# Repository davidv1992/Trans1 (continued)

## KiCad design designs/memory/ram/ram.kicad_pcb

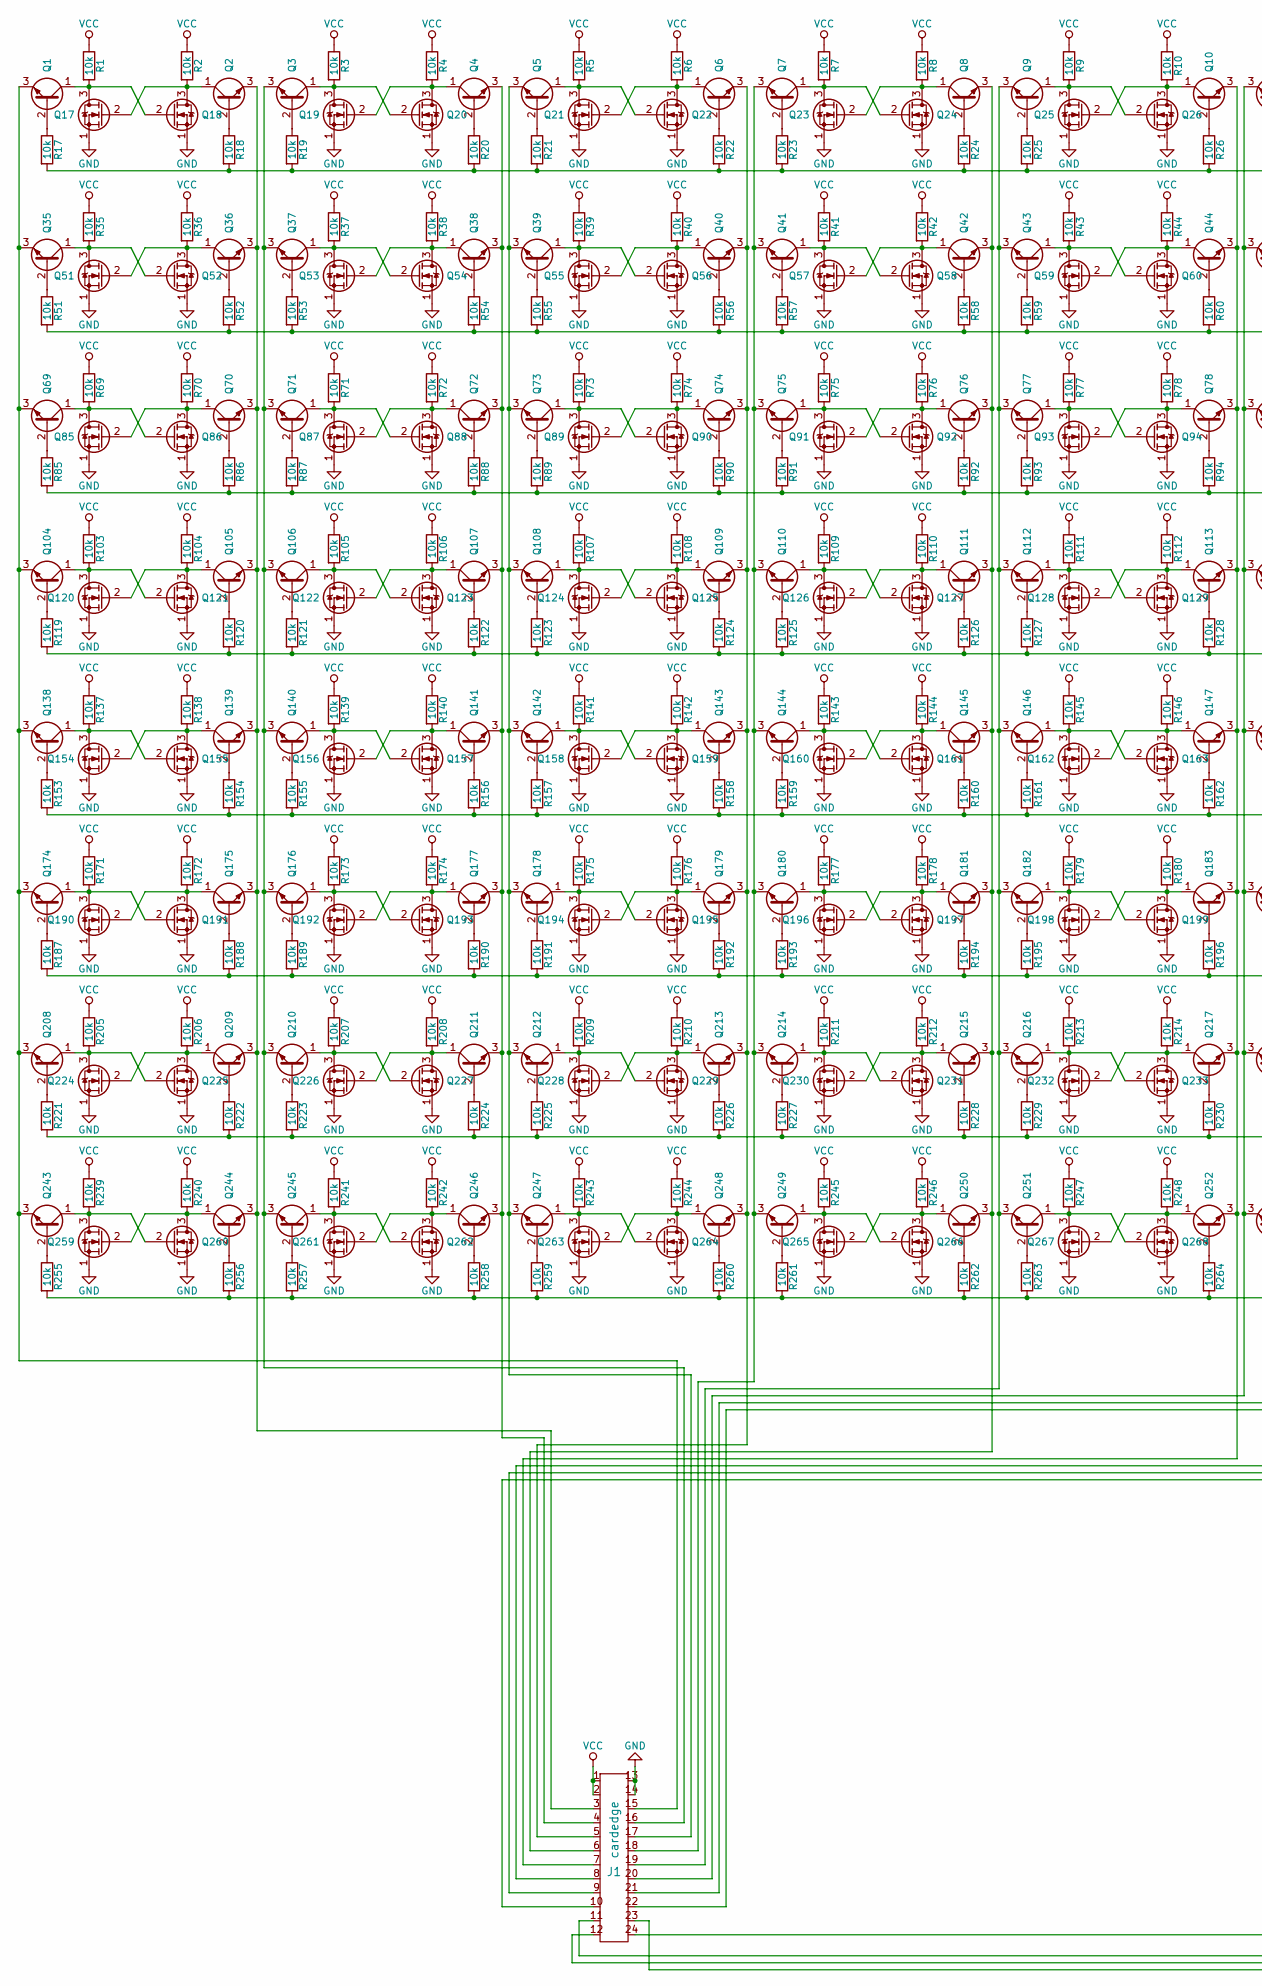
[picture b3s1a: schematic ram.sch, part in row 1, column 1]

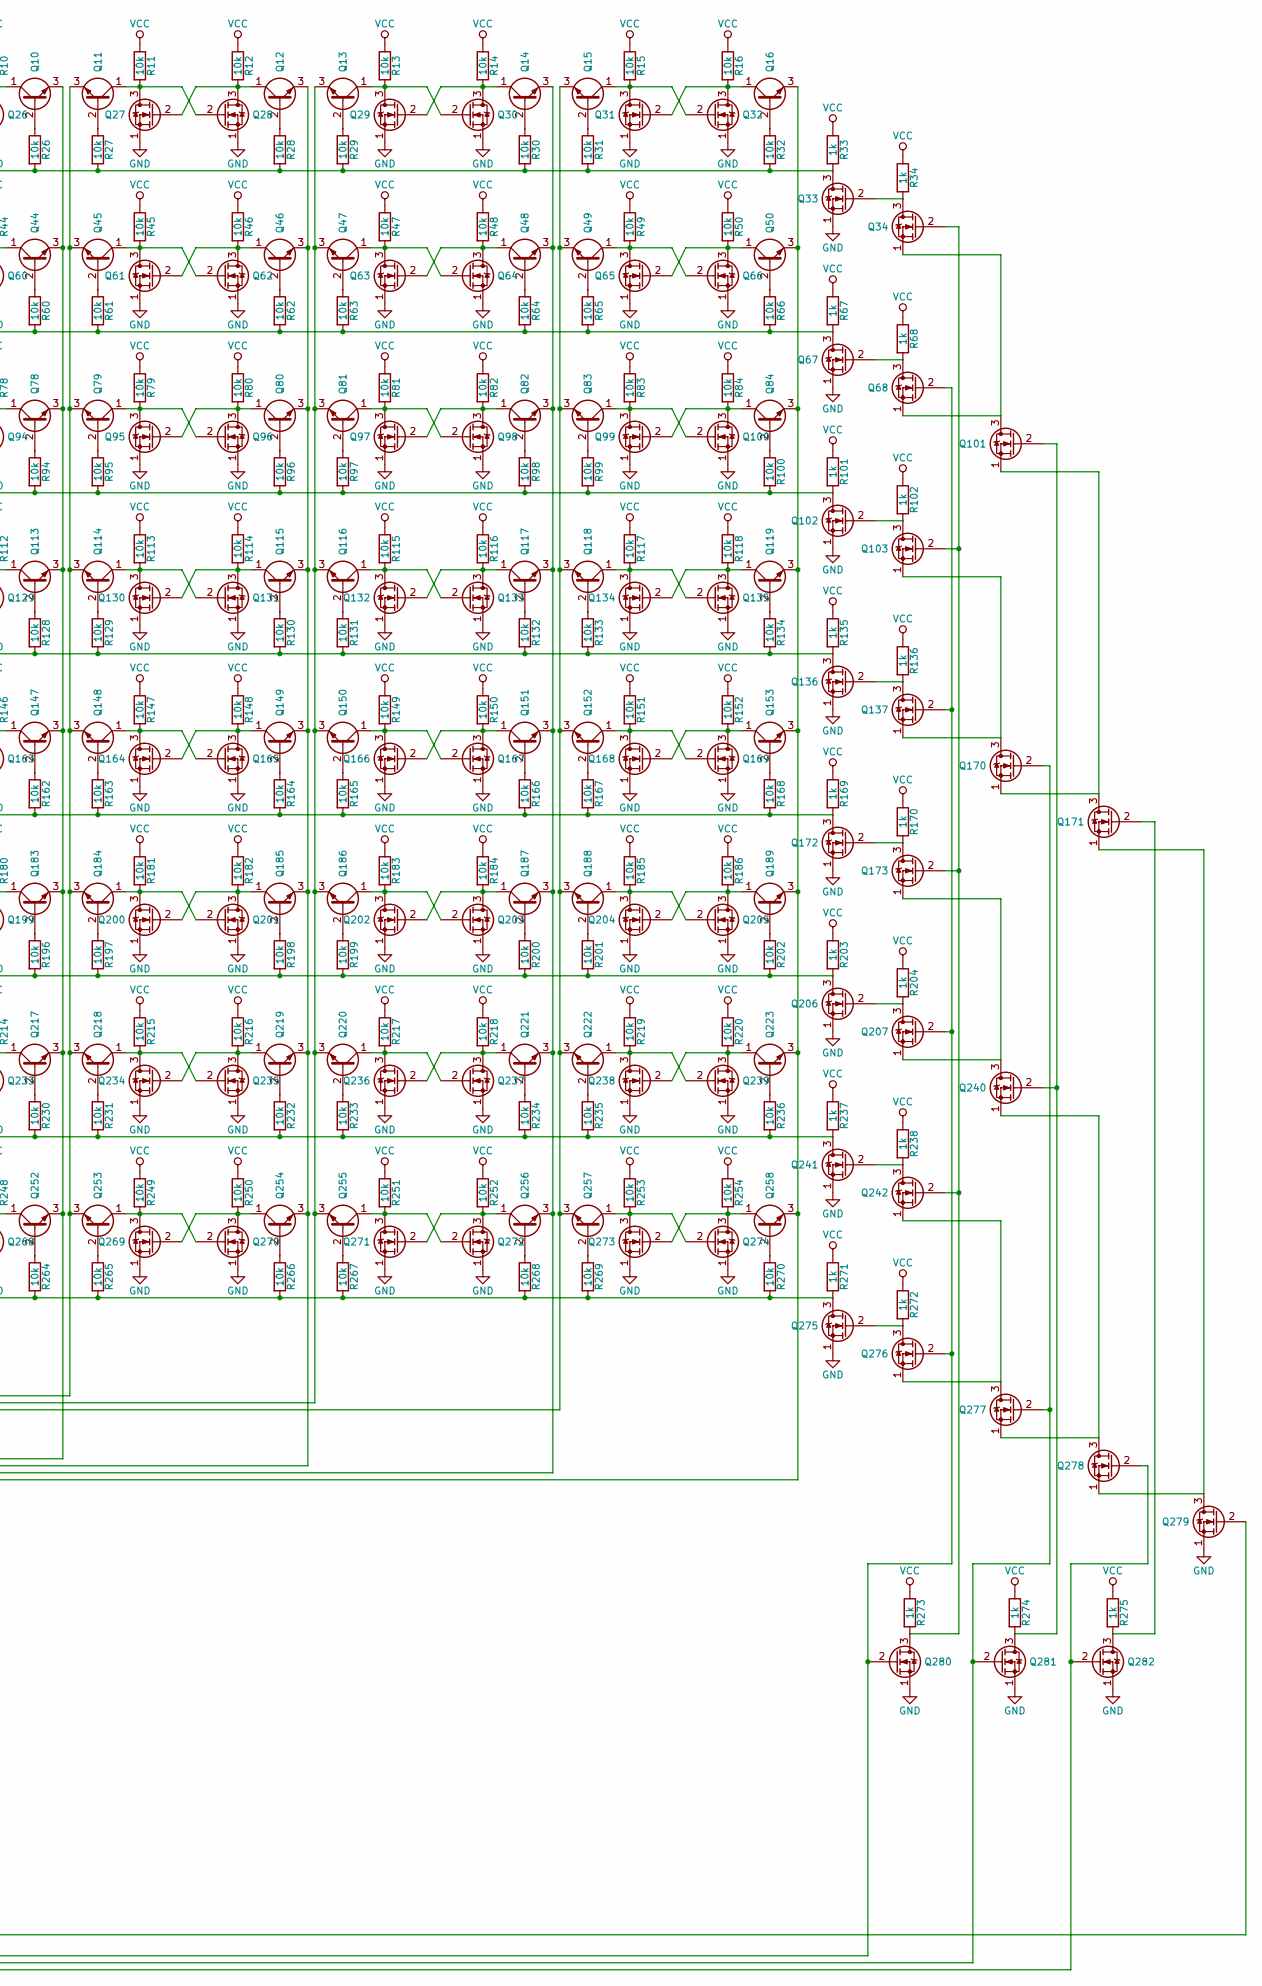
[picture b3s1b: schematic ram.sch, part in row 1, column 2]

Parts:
J1: cardedge; cardedge_12p
Q1, Q2, Q3, Q4, Q5, Q6, Q7, Q8, Q9, Q10, Q11, Q12, Q13, Q14, Q15, Q16, Q35, Q36, Q37, Q38, Q39, Q40, Q41, Q42, Q43, Q44, Q45, Q46, Q47, Q48, Q49, Q50, Q69, Q70, Q71, Q72, Q73, Q74, Q75, Q76, Q77, Q78, Q79, Q80, Q81, Q82, Q83, Q84, Q104, Q105, Q106, Q107, Q108, Q109, Q110, Q111, Q112, Q113, Q114, Q115, Q116, Q117, Q118, Q119, Q138, Q139, Q140, Q141, Q142, Q143, Q144, Q145, Q146, Q147, Q148, Q149, Q150, Q151, Q152, Q153, Q174, Q175, Q176, Q177, Q178, Q179, Q180, Q181, Q182, Q183, Q184, Q185, Q186, Q187, Q188, Q189, Q208, Q209, Q210, Q211, Q212, Q213, Q214, Q215, Q216, Q217, Q218, Q219, Q220, Q221, Q222, Q223, Q243, Q244, Q245, Q246, Q247, Q248, Q249, Q250, Q251, Q252, Q253, Q254, Q255, Q256, Q257, Q258: BC547; TO-92-BJT
Q17, Q18, Q19, Q20, Q21, Q22, Q23, Q24, Q25, Q26, Q27, Q28, Q29, Q30, Q31, Q32, Q33, Q34, Q51, Q52, Q53, Q54, Q55, Q56, Q57, Q58, Q59, Q60, Q61, Q62, Q63, Q64, Q65, Q66, Q67, Q68, Q85, Q86, Q87, Q88, Q89, Q90, Q91, Q92, Q93, Q94, Q95, Q96, Q97, Q98, Q99, Q100, Q101, Q102, Q103, Q120, Q121, Q122, Q123, Q124, Q125, Q126, Q127, Q128, Q129, Q130, Q131, Q132, Q133, Q134, Q135, Q136, Q137, Q154, Q155, Q156, Q157, Q158, Q159, Q160, Q161, Q162, Q163, Q164, Q165, Q166, Q167, Q168, Q169, Q170, Q171, Q172, Q173, Q190, Q191, Q192, Q193, Q194, Q195, Q196, Q197, Q198, Q199, Q200, Q201, Q202, Q203, Q204, Q205, Q206, Q207, Q224, Q225, Q226, Q227, Q228, Q229, Q230, Q231, Q232, Q233, Q234, Q235, Q236, Q237, Q238, Q239, Q240, Q241, Q242, Q259, Q260, Q261, Q262, Q263, Q264, Q265, Q266, Q267, Q268, Q269, Q270, Q271, Q272, Q273, Q274, Q275, Q276, Q277, Q278, Q279, Q280, Q281, Q282: 2N7000; TO-92-FET
R1, R2, R3, R4, R5, R6, R7, R8, R9, R10, R11, R12, R13, R14, R15, R16, R17, R18, R19, R20, R21, R22, R23, R24, R25, R26, R27, R28, R29, R30, R31, R32, R35, R36, R37, R38, R39, R40, R41, R42, R43, R44, R45, R46, R47, R48, R49, R50, R51, R52, R53, R54, R55, R56, R57, R58, R59, R60, R61, R62, R63, R64, R65, R66, R69, R70, R71, R72, R73, R74, R75, R76, R77, R78, R79, R80, R81, R82, R83, R84, R85, R86, R87, R88, R89, R90, R91, R92, R93, R94, R95, R96, R97, R98, R99, R100, R103, R104, R105, R106, R107, R108, R109, R110, R111, R112, R113, R114, R115, R116, R117, R118, R119, R120, R121, R122, R123, R124, R125, R126, R127, R128, R129, R130, R131, R132, R133, R134, R137, R138, R139, R140, R141, R142, R143, R144, R145, R146, R147, R148, R149, R150, R151, R152, R153, R154, R155, R156, R157, R158, R159, R160, R161, R162, R163, R164, R165, R166, R167, R168, R171, R172, R173, R174, R175, R176, R177, R178, R179, R180, R181, R182, R183, R184, R185, R186, R187, R188, R189, R190, R191, R192, R193, R194, R195, R196, R197, R198, R199, R200, R201, R202, R205, R206, R207, R208, R209, R210, R211, R212, R213, R214, R215, R216, R217, R218, R219, R220, R221, R222, R223, R224, R225, R226, R227, R228, R229, R230, R231, R232, R233, R234, R235, R236, R239, R240, R241, R242, R243, R244, R245, R246, R247, R248, R249, R250, R251, R252, R253, R254, R255, R256, R257, R258, R259, R260, R261, R262, R263, R264, R265, R266, R267, R268, R269, R270: 10k; R_small
R33, R34, R67, R68, R101, R102, R135, R136, R169, R170, R203, R204, R237, R238, R271, R272, R273, R274, R275: 1k; R_small

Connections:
GND: J1.13, J1.14, Q17.1 (S), Q18.1 (S), Q19.1 (S), Q20.1 (S), Q21.1 (S), Q22.1 (S), Q23.1 (S), Q24.1 (S), Q25.1 (S), Q26.1 (S), Q27.1 (S), Q28.1 (S), Q29.1 (S), Q30.1 (S), Q31.1 (S), Q32.1 (S), Q33.1 (S), Q51.1 (S), Q52.1 (S), Q53.1 (S), Q54.1 (S), Q55.1 (S), Q56.1 (S), Q57.1 (S), Q58.1 (S), Q59.1 (S), Q60.1 (S), Q61.1 (S), Q62.1 (S), Q63.1 (S), Q64.1 (S), Q65.1 (S), Q66.1 (S), Q67.1 (S), Q85.1 (S), Q86.1 (S), Q87.1 (S), Q88.1 (S), Q89.1 (S), Q90.1 (S), Q91.1 (S), Q92.1 (S), Q93.1 (S), Q94.1 (S), Q95.1 (S), Q96.1 (S), Q97.1 (S), Q98.1 (S), Q99.1 (S), Q100.1 (S), Q102.1 (S), Q120.1 (S), Q121.1 (S), Q122.1 (S), Q123.1 (S), Q124.1 (S), Q125.1 (S), Q126.1 (S), Q127.1 (S), Q128.1 (S), Q129.1 (S), Q130.1 (S), Q131.1 (S), Q132.1 (S), Q133.1 (S), Q134.1 (S), Q135.1 (S), Q136.1 (S), Q154.1 (S), Q155.1 (S), Q156.1 (S), Q157.1 (S), Q158.1 (S), Q159.1 (S), Q160.1 (S), Q161.1 (S), Q162.1 (S), Q163.1 (S), Q164.1 (S), Q165.1 (S), Q166.1 (S), Q167.1 (S), Q168.1 (S), Q169.1 (S), Q172.1 (S), Q190.1 (S), Q191.1 (S), Q192.1 (S), Q193.1 (S), Q194.1 (S), Q195.1 (S), Q196.1 (S), Q197.1 (S), Q198.1 (S), Q199.1 (S), Q200.1 (S), Q201.1 (S), Q202.1 (S), Q203.1 (S), Q204.1 (S), Q205.1 (S), Q206.1 (S), Q224.1 (S), Q225.1 (S), Q226.1 (S), Q227.1 (S), Q228.1 (S), Q229.1 (S), Q230.1 (S), Q231.1 (S), Q232.1 (S), Q233.1 (S), Q234.1 (S), Q235.1 (S), Q236.1 (S), Q237.1 (S), Q238.1 (S), Q239.1 (S), Q241.1 (S), Q259.1 (S), Q260.1 (S), Q261.1 (S), Q262.1 (S), Q263.1 (S), Q264.1 (S), Q265.1 (S), Q266.1 (S), Q267.1 (S), Q268.1 (S), Q269.1 (S), Q270.1 (S), Q271.1 (S), Q272.1 (S), Q273.1 (S), Q274.1 (S), Q275.1 (S), Q279.1 (S), Q280.1 (S), Q281.1 (S), Q282.1 (S)
unnamed: J1.3, Q2.3 (E), Q36.3 (E), Q70.3 (E), Q105.3 (E), Q139.3 (E), Q175.3 (E), Q209.3 (E), Q244.3 (E)
unnamed: J1.4, Q4.3 (E), Q38.3 (E), Q72.3 (E), Q107.3 (E), Q141.3 (E), Q177.3 (E), Q211.3 (E), Q246.3 (E)
unnamed: J1.5, Q6.3 (E), Q40.3 (E), Q74.3 (E), Q109.3 (E), Q143.3 (E), Q179.3 (E), Q213.3 (E), Q248.3 (E)
unnamed: J1.6, Q8.3 (E), Q42.3 (E), Q76.3 (E), Q111.3 (E), Q145.3 (E), Q181.3 (E), Q215.3 (E), Q250.3 (E)
unnamed: J1.7, Q10.3 (E), Q44.3 (E), Q78.3 (E), Q113.3 (E), Q147.3 (E), Q183.3 (E), Q217.3 (E), Q252.3 (E)
unnamed: J1.8, Q12.3 (E), Q46.3 (E), Q80.3 (E), Q115.3 (E), Q149.3 (E), Q185.3 (E), Q219.3 (E), Q254.3 (E)
unnamed: J1.9, Q14.3 (E), Q48.3 (E), Q82.3 (E), Q117.3 (E), Q151.3 (E), Q187.3 (E), Q221.3 (E), Q256.3 (E)
unnamed: J1.10, Q16.3 (E), Q50.3 (E), Q84.3 (E), Q119.3 (E), Q153.3 (E), Q189.3 (E), Q223.3 (E), Q258.3 (E)
unnamed: J1.11, Q68.2 (G), Q137.2 (G), Q207.2 (G), Q276.2 (G), Q280.2 (G)
unnamed: J1.12, Q170.2 (G), Q277.2 (G), Q281.2 (G)
unnamed: J1.15, Q1.3 (E), Q35.3 (E), Q69.3 (E), Q104.3 (E), Q138.3 (E), Q174.3 (E), Q208.3 (E), Q243.3 (E)
unnamed: J1.16, Q3.3 (E), Q37.3 (E), Q71.3 (E), Q106.3 (E), Q140.3 (E), Q176.3 (E), Q210.3 (E), Q245.3 (E)
unnamed: J1.17, Q5.3 (E), Q39.3 (E), Q73.3 (E), Q108.3 (E), Q142.3 (E), Q178.3 (E), Q212.3 (E), Q247.3 (E)
unnamed: J1.18, Q7.3 (E), Q41.3 (E), Q75.3 (E), Q110.3 (E), Q144.3 (E), Q180.3 (E), Q214.3 (E), Q249.3 (E)
unnamed: J1.19, Q9.3 (E), Q43.3 (E), Q77.3 (E), Q112.3 (E), Q146.3 (E), Q182.3 (E), Q216.3 (E), Q251.3 (E)
unnamed: J1.20, Q11.3 (E), Q45.3 (E), Q79.3 (E), Q114.3 (E), Q148.3 (E), Q184.3 (E), Q218.3 (E), Q253.3 (E)
unnamed: J1.21, Q13.3 (E), Q47.3 (E), Q81.3 (E), Q116.3 (E), Q150.3 (E), Q186.3 (E), Q220.3 (E), Q255.3 (E)
unnamed: J1.22, Q15.3 (E), Q49.3 (E), Q83.3 (E), Q118.3 (E), Q152.3 (E), Q188.3 (E), Q222.3 (E), Q257.3 (E)
unnamed: J1.23, Q278.2 (G), Q282.2 (G)
unnamed: J1.24, Q279.2 (G)
unnamed: Q1.1 (C), Q17.3 (D), Q18.2 (G), R1.2
unnamed: Q1.2 (B), R17.1
unnamed: Q2.2 (B), R18.1
unnamed: Q3.2 (B), R19.1
unnamed: Q4.2 (B), R20.1
unnamed: Q5.2 (B), R21.1
unnamed: Q6.2 (B), R22.1
unnamed: Q7.2 (B), R23.1
unnamed: Q8.2 (B), R24.1
unnamed: Q9.2 (B), R25.1
unnamed: Q10.1 (C), Q25.2 (G), Q26.3 (D), R10.2
unnamed: Q10.2 (B), R26.1
unnamed: Q11.1 (C), Q27.3 (D), Q28.2 (G), R11.2
unnamed: Q11.2 (B), R27.1
unnamed: Q12.1 (C), Q27.2 (G), Q28.3 (D), R12.2
unnamed: Q12.2 (B), R28.1
unnamed: Q13.1 (C), Q29.3 (D), Q30.2 (G), R13.2
unnamed: Q13.2 (B), R29.1
unnamed: Q14.1 (C), Q29.2 (G), Q30.3 (D), R14.2
unnamed: Q14.2 (B), R30.1
unnamed: Q15.1 (C), Q31.3 (D), Q32.2 (G), R15.2
unnamed: Q15.2 (B), R31.1
unnamed: Q16.1 (C), Q31.2 (G), Q32.3 (D), R16.2
unnamed: Q16.2 (B), R32.1
unnamed: Q2.1 (C), Q17.2 (G), Q18.3 (D), R2.2
unnamed: Q4.1 (C), Q19.2 (G), Q20.3 (D), R4.2
unnamed: Q3.1 (C), Q19.3 (D), Q20.2 (G), R3.2
unnamed: Q6.1 (C), Q21.2 (G), Q22.3 (D), R6.2
unnamed: Q5.1 (C), Q21.3 (D), Q22.2 (G), R5.2
unnamed: Q8.1 (C), Q23.2 (G), Q24.3 (D), R8.2
unnamed: Q7.1 (C), Q23.3 (D), Q24.2 (G), R7.2
unnamed: Q9.1 (C), Q25.3 (D), Q26.2 (G), R9.2
unnamed: Q33.2 (G), Q34.3 (D), R34.2
unnamed: Q33.3 (D), R17.2, R18.2, R19.2, R20.2, R21.2, R22.2, R23.2, R24.2, R25.2, R26.2, R27.2, R28.2, R29.2, R30.2, R31.2, R32.2, R33.2
unnamed: Q35.1 (C), Q51.3 (D), Q52.2 (G), R35.2
unnamed: Q35.2 (B), R51.1
unnamed: Q36.1 (C), Q51.2 (G), Q52.3 (D), R36.2
unnamed: Q36.2 (B), R52.1
unnamed: Q37.1 (C), Q53.3 (D), Q54.2 (G), R37.2
unnamed: Q37.2 (B), R53.1
unnamed: Q38.1 (C), Q53.2 (G), Q54.3 (D), R38.2
unnamed: Q38.2 (B), R54.1
unnamed: Q39.1 (C), Q55.3 (D), Q56.2 (G), R39.2
unnamed: Q39.2 (B), R55.1
unnamed: Q40.1 (C), Q55.2 (G), Q56.3 (D), R40.2
unnamed: Q40.2 (B), R56.1
unnamed: Q41.1 (C), Q57.3 (D), Q58.2 (G), R41.2
unnamed: Q41.2 (B), R57.1
unnamed: Q42.1 (C), Q57.2 (G), Q58.3 (D), R42.2
unnamed: Q42.2 (B), R58.1
unnamed: Q43.1 (C), Q59.3 (D), Q60.2 (G), R43.2
unnamed: Q43.2 (B), R59.1
unnamed: Q44.1 (C), Q59.2 (G), Q60.3 (D), R44.2
unnamed: Q44.2 (B), R60.1
unnamed: Q45.1 (C), Q61.3 (D), Q62.2 (G), R45.2
unnamed: Q45.2 (B), R61.1
unnamed: Q46.1 (C), Q61.2 (G), Q62.3 (D), R46.2
unnamed: Q46.2 (B), R62.1
unnamed: Q47.1 (C), Q63.3 (D), Q64.2 (G), R47.2
unnamed: Q47.2 (B), R63.1
unnamed: Q48.1 (C), Q63.2 (G), Q64.3 (D), R48.2
unnamed: Q48.2 (B), R64.1
unnamed: Q49.1 (C), Q65.3 (D), Q66.2 (G), R49.2
unnamed: Q49.2 (B), R65.1
unnamed: Q50.1 (C), Q65.2 (G), Q66.3 (D), R50.2
unnamed: Q50.2 (B), R66.1
unnamed: Q67.2 (G), Q68.3 (D), R68.2
unnamed: Q67.3 (D), R51.2, R52.2, R53.2, R54.2, R55.2, R56.2, R57.2, R58.2, R59.2, R60.2, R61.2, R62.2, R63.2, R64.2, R65.2, R66.2, R67.2
unnamed: Q69.1 (C), Q85.3 (D), Q86.2 (G), R69.2
unnamed: Q69.2 (B), R85.1
unnamed: Q70.1 (C), Q85.2 (G), Q86.3 (D), R70.2
unnamed: Q70.2 (B), R86.1
unnamed: Q71.1 (C), Q87.3 (D), Q88.2 (G), R71.2
unnamed: Q71.2 (B), R87.1
unnamed: Q72.1 (C), Q87.2 (G), Q88.3 (D), R72.2
unnamed: Q72.2 (B), R88.1
unnamed: Q73.1 (C), Q89.3 (D), Q90.2 (G), R73.2
unnamed: Q73.2 (B), R89.1
unnamed: Q74.1 (C), Q89.2 (G), Q90.3 (D), R74.2
unnamed: Q74.2 (B), R90.1
unnamed: Q75.1 (C), Q91.3 (D), Q92.2 (G), R75.2
unnamed: Q75.2 (B), R91.1
unnamed: Q76.1 (C), Q91.2 (G), Q92.3 (D), R76.2
unnamed: Q76.2 (B), R92.1
unnamed: Q77.1 (C), Q93.3 (D), Q94.2 (G), R77.2
unnamed: Q77.2 (B), R93.1
unnamed: Q78.1 (C), Q93.2 (G), Q94.3 (D), R78.2
unnamed: Q78.2 (B), R94.1
unnamed: Q79.1 (C), Q95.3 (D), Q96.2 (G), R79.2
unnamed: Q79.2 (B), R95.1
unnamed: Q80.1 (C), Q95.2 (G), Q96.3 (D), R80.2
unnamed: Q80.2 (B), R96.1
unnamed: Q81.1 (C), Q97.3 (D), Q98.2 (G), R81.2
unnamed: Q81.2 (B), R97.1
unnamed: Q82.1 (C), Q97.2 (G), Q98.3 (D), R82.2
unnamed: Q82.2 (B), R98.1
unnamed: Q83.2 (B), R99.1
unnamed: Q84.2 (B), R100.1
unnamed: Q83.1 (C), Q99.3 (D), Q100.2 (G), R83.2
unnamed: Q84.1 (C), Q99.2 (G), Q100.3 (D), R84.2
unnamed: Q101.1 (S), Q170.1 (S), Q171.3 (D)
unnamed: Q101.2 (G), Q240.2 (G), Q281.3 (D), R274.2
unnamed: Q34.1 (S), Q68.1 (S), Q101.3 (D)
unnamed: Q102.2 (G), Q103.3 (D), R102.2
unnamed: Q102.3 (D), R85.2, R86.2, R87.2, R88.2, R89.2, R90.2, R91.2, R92.2, R93.2, R94.2, R95.2, R96.2, R97.2, R98.2, R99.2, R100.2, R101.2
unnamed: Q103.1 (S), Q137.1 (S), Q170.3 (D)
unnamed: Q34.2 (G), Q103.2 (G), Q173.2 (G), Q242.2 (G), Q280.3 (D), R273.2
unnamed: Q104.1 (C), Q120.3 (D), Q121.2 (G), R103.2
unnamed: Q104.2 (B), R119.1
unnamed: Q105.1 (C), Q120.2 (G), Q121.3 (D), R104.2
unnamed: Q105.2 (B), R120.1
unnamed: Q106.1 (C), Q122.3 (D), Q123.2 (G), R105.2
unnamed: Q106.2 (B), R121.1
unnamed: Q107.1 (C), Q122.2 (G), Q123.3 (D), R106.2
unnamed: Q107.2 (B), R122.1
unnamed: Q108.1 (C), Q124.3 (D), Q125.2 (G), R107.2
unnamed: Q108.2 (B), R123.1
unnamed: Q109.1 (C), Q124.2 (G), Q125.3 (D), R108.2
unnamed: Q109.2 (B), R124.1
unnamed: Q110.1 (C), Q126.3 (D), Q127.2 (G), R109.2
unnamed: Q110.2 (B), R125.1
unnamed: Q111.1 (C), Q126.2 (G), Q127.3 (D), R110.2
unnamed: Q111.2 (B), R126.1
unnamed: Q112.1 (C), Q128.3 (D), Q129.2 (G), R111.2
unnamed: Q112.2 (B), R127.1
unnamed: Q113.1 (C), Q128.2 (G), Q129.3 (D), R112.2
unnamed: Q113.2 (B), R128.1
unnamed: Q114.1 (C), Q130.3 (D), Q131.2 (G), R113.2
unnamed: Q114.2 (B), R129.1
unnamed: Q115.1 (C), Q130.2 (G), Q131.3 (D), R114.2
unnamed: Q115.2 (B), R130.1
unnamed: Q116.1 (C), Q132.3 (D), Q133.2 (G), R115.2
unnamed: Q116.2 (B), R131.1
unnamed: Q117.1 (C), Q132.2 (G), Q133.3 (D), R116.2
unnamed: Q117.2 (B), R132.1
unnamed: Q118.1 (C), Q134.3 (D), Q135.2 (G), R117.2
unnamed: Q118.2 (B), R133.1
unnamed: Q119.1 (C), Q134.2 (G), Q135.3 (D), R118.2
unnamed: Q119.2 (B), R134.1
unnamed: Q136.2 (G), Q137.3 (D), R136.2
unnamed: Q136.3 (D), R119.2, R120.2, R121.2, R122.2, R123.2, R124.2, R125.2, R126.2, R127.2, R128.2, R129.2, R130.2, R131.2, R132.2, R133.2, R134.2, R135.2
unnamed: Q138.1 (C), Q154.3 (D), Q155.2 (G), R137.2
unnamed: Q138.2 (B), R153.1
unnamed: Q139.1 (C), Q154.2 (G), Q155.3 (D), R138.2
unnamed: Q139.2 (B), R154.1
unnamed: Q140.1 (C), Q156.3 (D), Q157.2 (G), R139.2
unnamed: Q140.2 (B), R155.1
unnamed: Q141.1 (C), Q156.2 (G), Q157.3 (D), R140.2
unnamed: Q141.2 (B), R156.1
unnamed: Q142.1 (C), Q158.3 (D), Q159.2 (G), R141.2
unnamed: Q142.2 (B), R157.1
unnamed: Q143.1 (C), Q158.2 (G), Q159.3 (D), R142.2
unnamed: Q143.2 (B), R158.1
unnamed: Q144.1 (C), Q160.3 (D), Q161.2 (G), R143.2
unnamed: Q144.2 (B), R159.1
unnamed: Q145.1 (C), Q160.2 (G), Q161.3 (D), R144.2
unnamed: Q145.2 (B), R160.1
unnamed: Q146.1 (C), Q162.3 (D), Q163.2 (G), R145.2
unnamed: Q146.2 (B), R161.1
unnamed: Q147.1 (C), Q162.2 (G), Q163.3 (D), R146.2
unnamed: Q147.2 (B), R162.1
unnamed: Q148.1 (C), Q164.3 (D), Q165.2 (G), R147.2
unnamed: Q148.2 (B), R163.1
unnamed: Q149.1 (C), Q164.2 (G), Q165.3 (D), R148.2
unnamed: Q149.2 (B), R164.1
unnamed: Q150.1 (C), Q166.3 (D), Q167.2 (G), R149.2
unnamed: Q150.2 (B), R165.1
unnamed: Q151.1 (C), Q166.2 (G), Q167.3 (D), R150.2
unnamed: Q151.2 (B), R166.1
unnamed: Q152.1 (C), Q168.3 (D), Q169.2 (G), R151.2
unnamed: Q152.2 (B), R167.1
unnamed: Q153.1 (C), Q168.2 (G), Q169.3 (D), R152.2
unnamed: Q153.2 (B), R168.1
unnamed: Q171.1 (S), Q278.1 (S), Q279.3 (D)
unnamed: Q171.2 (G), Q282.3 (D), R275.2
unnamed: Q172.2 (G), Q173.3 (D), R170.2
unnamed: Q172.3 (D), R153.2, R154.2, R155.2, R156.2, R157.2, R158.2, R159.2, R160.2, R161.2, R162.2, R163.2, R164.2, R165.2, R166.2, R167.2, R168.2, R169.2
unnamed: Q173.1 (S), Q207.1 (S), Q240.3 (D)
unnamed: Q174.1 (C), Q190.3 (D), Q191.2 (G), R171.2
unnamed: Q174.2 (B), R187.1
unnamed: Q175.1 (C), Q190.2 (G), Q191.3 (D), R172.2
unnamed: Q175.2 (B), R188.1
unnamed: Q176.1 (C), Q192.3 (D), Q193.2 (G), R173.2
unnamed: Q176.2 (B), R189.1
unnamed: Q177.1 (C), Q192.2 (G), Q193.3 (D), R174.2
unnamed: Q177.2 (B), R190.1
unnamed: Q178.1 (C), Q194.3 (D), Q195.2 (G), R175.2
unnamed: Q178.2 (B), R191.1
unnamed: Q179.1 (C), Q194.2 (G), Q195.3 (D), R176.2
unnamed: Q179.2 (B), R192.1
unnamed: Q180.1 (C), Q196.3 (D), Q197.2 (G), R177.2
unnamed: Q180.2 (B), R193.1
unnamed: Q181.1 (C), Q196.2 (G), Q197.3 (D), R178.2
unnamed: Q181.2 (B), R194.1
unnamed: Q182.1 (C), Q198.3 (D), Q199.2 (G), R179.2
unnamed: Q182.2 (B), R195.1
unnamed: Q183.1 (C), Q198.2 (G), Q199.3 (D), R180.2
unnamed: Q183.2 (B), R196.1
unnamed: Q184.1 (C), Q200.3 (D), Q201.2 (G), R181.2
unnamed: Q184.2 (B), R197.1
unnamed: Q185.1 (C), Q200.2 (G), Q201.3 (D), R182.2
unnamed: Q185.2 (B), R198.1
unnamed: Q186.1 (C), Q202.3 (D), Q203.2 (G), R183.2
unnamed: Q186.2 (B), R199.1
unnamed: Q187.1 (C), Q202.2 (G), Q203.3 (D), R184.2
unnamed: Q187.2 (B), R200.1
unnamed: Q188.1 (C), Q204.3 (D), Q205.2 (G), R185.2
unnamed: Q188.2 (B), R201.1
unnamed: Q189.1 (C), Q204.2 (G), Q205.3 (D), R186.2
unnamed: Q189.2 (B), R202.1
unnamed: Q206.2 (G), Q207.3 (D), R204.2
unnamed: Q206.3 (D), R187.2, R188.2, R189.2, R190.2, R191.2, R192.2, R193.2, R194.2, R195.2, R196.2, R197.2, R198.2, R199.2, R200.2, R201.2, R202.2, R203.2
unnamed: Q208.1 (C), Q224.3 (D), Q225.2 (G), R205.2
unnamed: Q208.2 (B), R221.1
unnamed: Q209.1 (C), Q224.2 (G), Q225.3 (D), R206.2
unnamed: Q209.2 (B), R222.1
unnamed: Q210.1 (C), Q226.3 (D), Q227.2 (G), R207.2
unnamed: Q210.2 (B), R223.1
unnamed: Q211.1 (C), Q226.2 (G), Q227.3 (D), R208.2
unnamed: Q211.2 (B), R224.1
unnamed: Q212.1 (C), Q228.3 (D), Q229.2 (G), R209.2
unnamed: Q212.2 (B), R225.1
unnamed: Q213.1 (C), Q228.2 (G), Q229.3 (D), R210.2
unnamed: Q213.2 (B), R226.1
unnamed: Q214.1 (C), Q230.3 (D), Q231.2 (G), R211.2
unnamed: Q214.2 (B), R227.1
unnamed: Q215.1 (C), Q230.2 (G), Q231.3 (D), R212.2
unnamed: Q215.2 (B), R228.1
unnamed: Q216.1 (C), Q232.3 (D), Q233.2 (G), R213.2
unnamed: Q216.2 (B), R229.1
unnamed: Q217.1 (C), Q232.2 (G), Q233.3 (D), R214.2
unnamed: Q217.2 (B), R230.1
unnamed: Q218.1 (C), Q234.3 (D), Q235.2 (G), R215.2
unnamed: Q218.2 (B), R231.1
unnamed: Q219.1 (C), Q234.2 (G), Q235.3 (D), R216.2
unnamed: Q219.2 (B), R232.1
unnamed: Q220.1 (C), Q236.3 (D), Q237.2 (G), R217.2
unnamed: Q220.2 (B), R233.1
unnamed: Q221.1 (C), Q236.2 (G), Q237.3 (D), R218.2
unnamed: Q221.2 (B), R234.1
unnamed: Q222.1 (C), Q238.3 (D), Q239.2 (G), R219.2
unnamed: Q222.2 (B), R235.1
unnamed: Q223.1 (C), Q238.2 (G), Q239.3 (D), R220.2
unnamed: Q223.2 (B), R236.1
unnamed: Q240.1 (S), Q277.1 (S), Q278.3 (D)
unnamed: Q241.2 (G), Q242.3 (D), R238.2
unnamed: Q241.3 (D), R221.2, R222.2, R223.2, R224.2, R225.2, R226.2, R227.2, R228.2, R229.2, R230.2, R231.2, R232.2, R233.2, R234.2, R235.2, R236.2, R237.2
unnamed: Q242.1 (S), Q276.1 (S), Q277.3 (D)
unnamed: Q243.1 (C), Q259.3 (D), Q260.2 (G), R239.2
unnamed: Q243.2 (B), R255.1
unnamed: Q244.1 (C), Q259.2 (G), Q260.3 (D), R240.2
unnamed: Q244.2 (B), R256.1
unnamed: Q245.1 (C), Q261.3 (D), Q262.2 (G), R241.2
unnamed: Q245.2 (B), R257.1
unnamed: Q246.1 (C), Q261.2 (G), Q262.3 (D), R242.2
unnamed: Q246.2 (B), R258.1
unnamed: Q247.1 (C), Q263.3 (D), Q264.2 (G), R243.2
unnamed: Q247.2 (B), R259.1
unnamed: Q248.1 (C), Q263.2 (G), Q264.3 (D), R244.2
unnamed: Q248.2 (B), R260.1
unnamed: Q249.1 (C), Q265.3 (D), Q266.2 (G), R245.2
unnamed: Q249.2 (B), R261.1
unnamed: Q250.1 (C), Q265.2 (G), Q266.3 (D), R246.2
unnamed: Q250.2 (B), R262.1
unnamed: Q251.1 (C), Q267.3 (D), Q268.2 (G), R247.2
unnamed: Q251.2 (B), R263.1
unnamed: Q252.1 (C), Q267.2 (G), Q268.3 (D), R248.2
unnamed: Q252.2 (B), R264.1
unnamed: Q253.1 (C), Q269.3 (D), Q270.2 (G), R249.2
unnamed: Q253.2 (B), R265.1
unnamed: Q254.1 (C), Q269.2 (G), Q270.3 (D), R250.2
unnamed: Q254.2 (B), R266.1
unnamed: Q255.1 (C), Q271.3 (D), Q272.2 (G), R251.2
unnamed: Q255.2 (B), R267.1
unnamed: Q256.1 (C), Q271.2 (G), Q272.3 (D), R252.2
unnamed: Q256.2 (B), R268.1
unnamed: Q257.1 (C), Q273.3 (D), Q274.2 (G), R253.2
unnamed: Q257.2 (B), R269.1
unnamed: Q258.1 (C), Q273.2 (G), Q274.3 (D), R254.2
unnamed: Q258.2 (B), R270.1
unnamed: Q275.2 (G), Q276.3 (D), R272.2
unnamed: Q275.3 (D), R255.2, R256.2, R257.2, R258.2, R259.2, R260.2, R261.2, R262.2, R263.2, R264.2, R265.2, R266.2, R267.2, R268.2, R269.2, R270.2, R271.2
VCC: J1.1, J1.2, R1.1, R2.1, R3.1, R4.1, R5.1, R6.1, R7.1, R8.1, R9.1, R10.1, R11.1, R12.1, R13.1, R14.1, R15.1, R16.1, R33.1, R34.1, R35.1, R36.1, R37.1, R38.1, R39.1, R40.1, R41.1, R42.1, R43.1, R44.1, R45.1, R46.1, R47.1, R48.1, R49.1, R50.1, R67.1, R68.1, R69.1, R70.1, R71.1, R72.1, R73.1, R74.1, R75.1, R76.1, R77.1, R78.1, R79.1, R80.1, R81.1, R82.1, R83.1, R84.1, R101.1, R102.1, R103.1, R104.1, R105.1, R106.1, R107.1, R108.1, R109.1, R110.1, R111.1, R112.1, R113.1, R114.1, R115.1, R116.1, R117.1, R118.1, R135.1, R136.1, R137.1, R138.1, R139.1, R140.1, R141.1, R142.1, R143.1, R144.1, R145.1, R146.1, R147.1, R148.1, R149.1, R150.1, R151.1, R152.1, R169.1, R170.1, R171.1, R172.1, R173.1, R174.1, R175.1, R176.1, R177.1, R178.1, R179.1, R180.1, R181.1, R182.1, R183.1, R184.1, R185.1, R186.1, R203.1, R204.1, R205.1, R206.1, R207.1, R208.1, R209.1, R210.1, R211.1, R212.1, R213.1, R214.1, R215.1, R216.1, R217.1, R218.1, R219.1, R220.1, R237.1, R238.1, R239.1, R240.1, R241.1, R242.1, R243.1, R244.1, R245.1, R246.1, R247.1, R248.1, R249.1, R250.1, R251.1, R252.1, R253.1, R254.1, R271.1, R272.1, R273.1, R274.1, R275.1

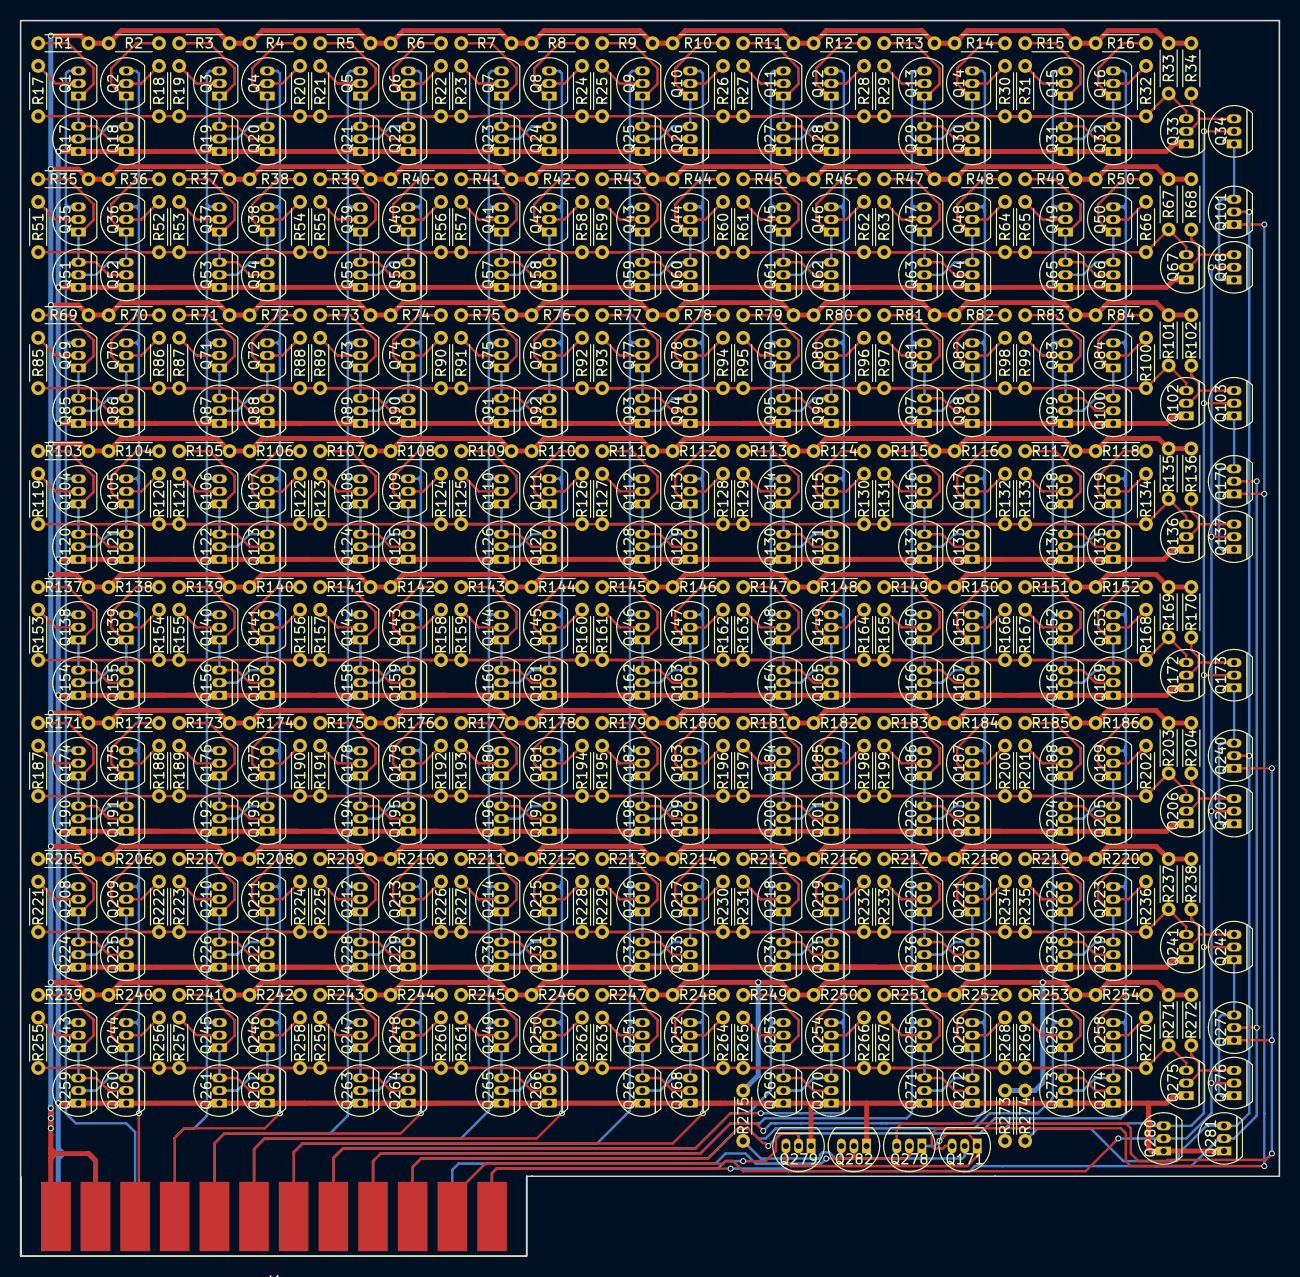
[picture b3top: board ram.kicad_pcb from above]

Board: 2 copper layers, 127.0 x 124.6 mm, 558 parts (0 on the bottom side), 304 nets.

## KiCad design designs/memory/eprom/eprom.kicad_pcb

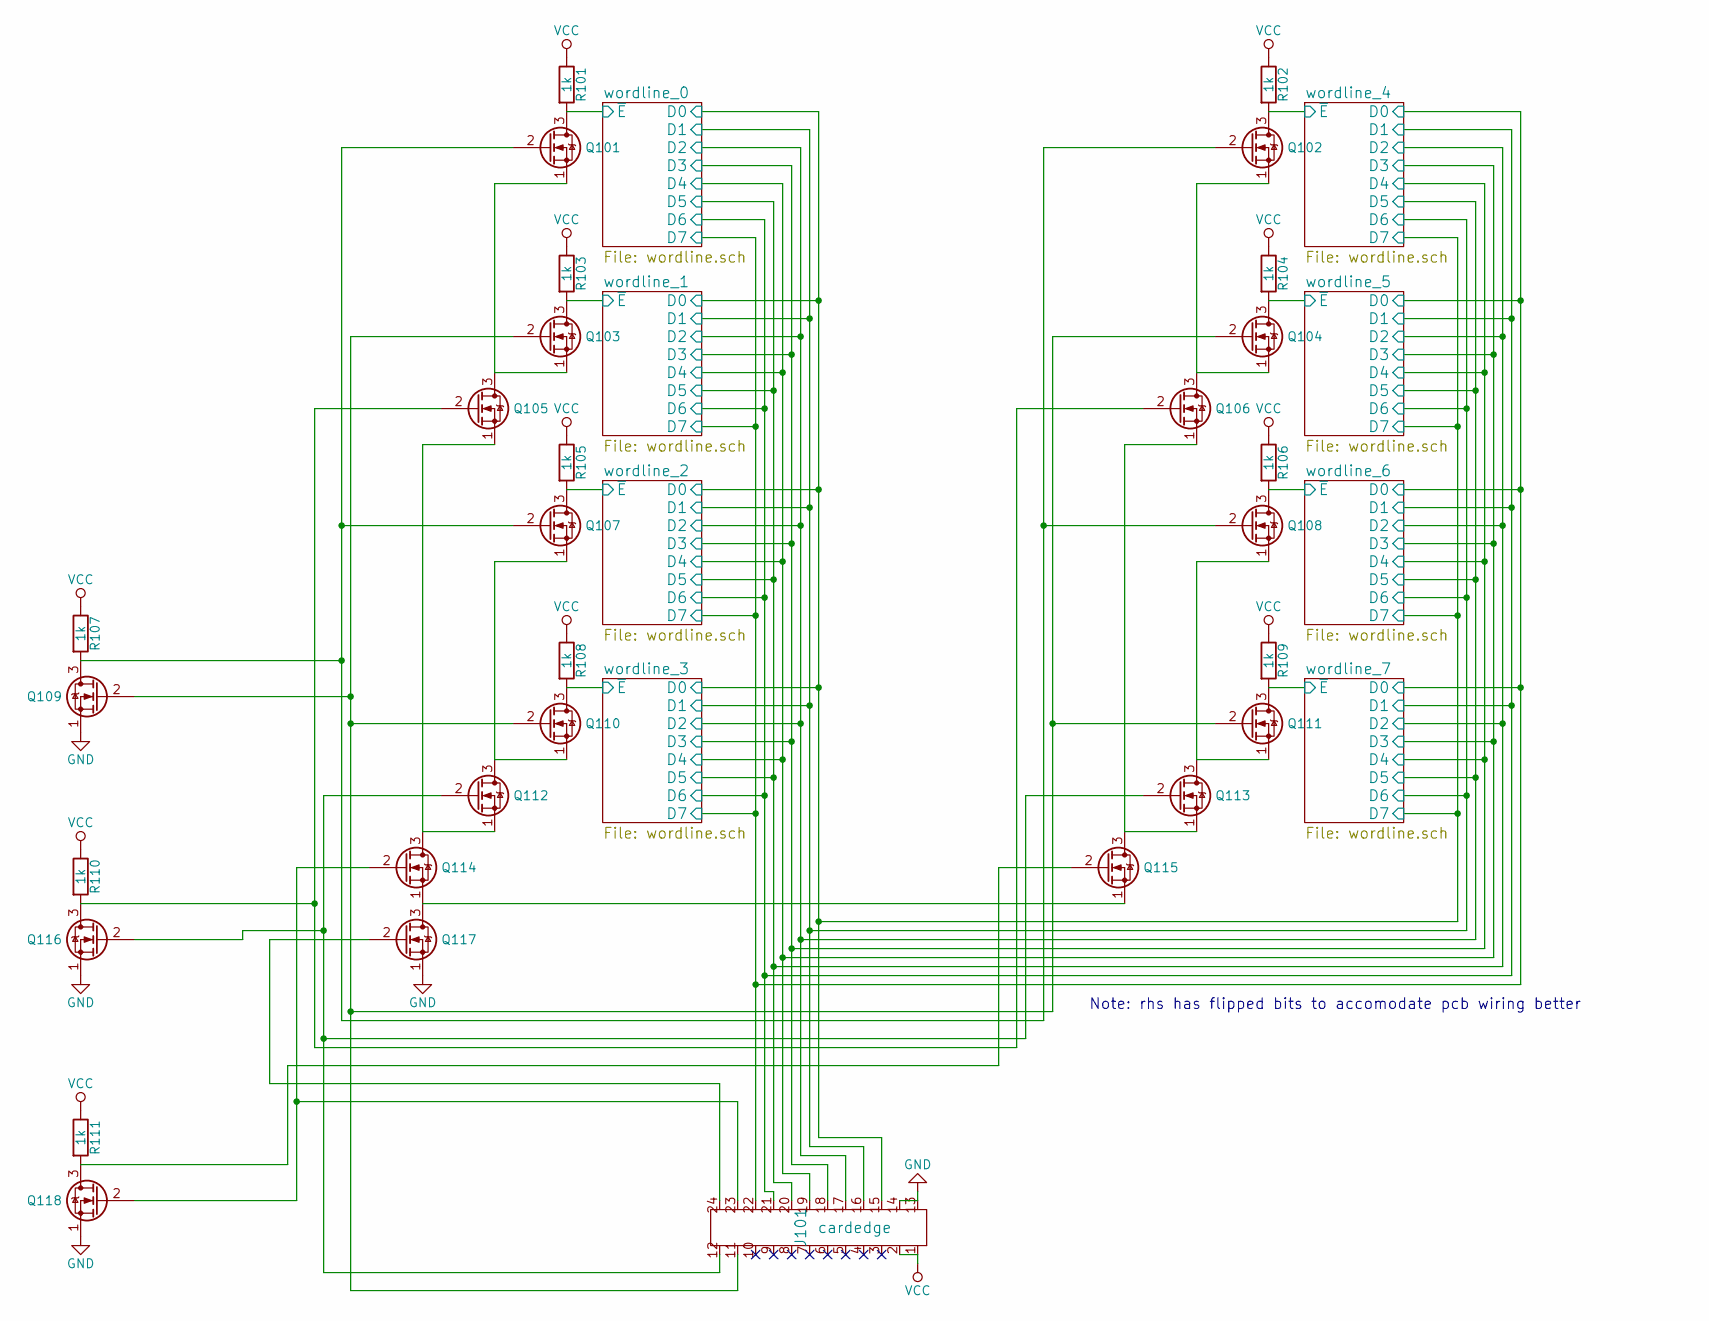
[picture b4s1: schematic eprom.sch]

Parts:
J101: cardedge; cardedge_12p
Q101, Q102, Q103, Q104, Q105, Q106, Q107, Q108, Q109, Q110, Q111, Q112, Q113, Q114, Q115, Q116, Q117, Q118: 2N7000; TO-92-FET
R101, R102, R103, R104, R105, R106, R107, R108, R109, R110, R111: 1k; R_small

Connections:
/wordline_0/D0: J101.15; also elsewhere on the board
/wordline_0/D1: J101.16; also elsewhere on the board
/wordline_0/D2: J101.17; also elsewhere on the board
/wordline_0/D3: J101.18; also elsewhere on the board
/wordline_0/~E: Q101.3 (D), R101.2; also elsewhere on the board
/wordline_1/~E: Q103.3 (D), R103.2; also elsewhere on the board
/wordline_2/~E: Q107.3 (D), R105.2; also elsewhere on the board
/wordline_3/~E: Q110.3 (D), R108.2; also elsewhere on the board
/wordline_4/D0: J101.22; also elsewhere on the board
/wordline_4/D1: J101.21; also elsewhere on the board
/wordline_4/D2: J101.20; also elsewhere on the board
/wordline_4/D3: J101.19; also elsewhere on the board
/wordline_4/~E: Q102.3 (D), R102.2; also elsewhere on the board
/wordline_5/~E: Q104.3 (D), R104.2; also elsewhere on the board
/wordline_6/~E: Q108.3 (D), R106.2; also elsewhere on the board
/wordline_7/~E: Q111.3 (D), R109.2; also elsewhere on the board
GND: J101.13, J101.14, Q109.1 (S), Q116.1 (S), Q117.1 (S), Q118.1 (S); also elsewhere on the board
unnamed: J101.11, Q103.2 (G), Q104.2 (G), Q109.2 (G), Q110.2 (G), Q111.2 (G)
unnamed: J101.12, Q112.2 (G), Q113.2 (G), Q116.2 (G)
unnamed: J101.23, Q114.2 (G), Q118.2 (G)
unnamed: J101.24, Q117.2 (G)
unnamed: Q101.1 (S), Q103.1 (S), Q105.3 (D)
unnamed: Q101.2 (G), Q102.2 (G), Q107.2 (G), Q108.2 (G), Q109.3 (D), R107.2
unnamed: Q102.1 (S), Q104.1 (S), Q106.3 (D)
unnamed: Q105.1 (S), Q112.1 (S), Q114.3 (D)
unnamed: Q105.2 (G), Q106.2 (G), Q116.3 (D), R110.2
unnamed: Q106.1 (S), Q113.1 (S), Q115.3 (D)
unnamed: Q107.1 (S), Q110.1 (S), Q112.3 (D)
unnamed: Q108.1 (S), Q111.1 (S), Q113.3 (D)
unnamed: Q114.1 (S), Q115.1 (S), Q117.3 (D)
unnamed: Q115.2 (G), Q118.3 (D), R111.2
VCC: J101.1, J101.2, R101.1, R102.1, R103.1, R104.1, R105.1, R106.1, R107.1, R108.1, R109.1, R110.1, R111.1; also elsewhere on the board

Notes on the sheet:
Note: rhs has flipped bits to accomodate pcb wiring better
